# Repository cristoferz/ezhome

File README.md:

# ezHome Project 

This is the home for the ezHome team's development.

### Project status

For now, the project is on the beginning so there's not much to talk about.
We are developing the basis for customization capabilitys, communication standarts and somethings like that. 

More details can be founded on Issues.

## See also ##
[Project Pieces](PROJECT_PIECES.md)

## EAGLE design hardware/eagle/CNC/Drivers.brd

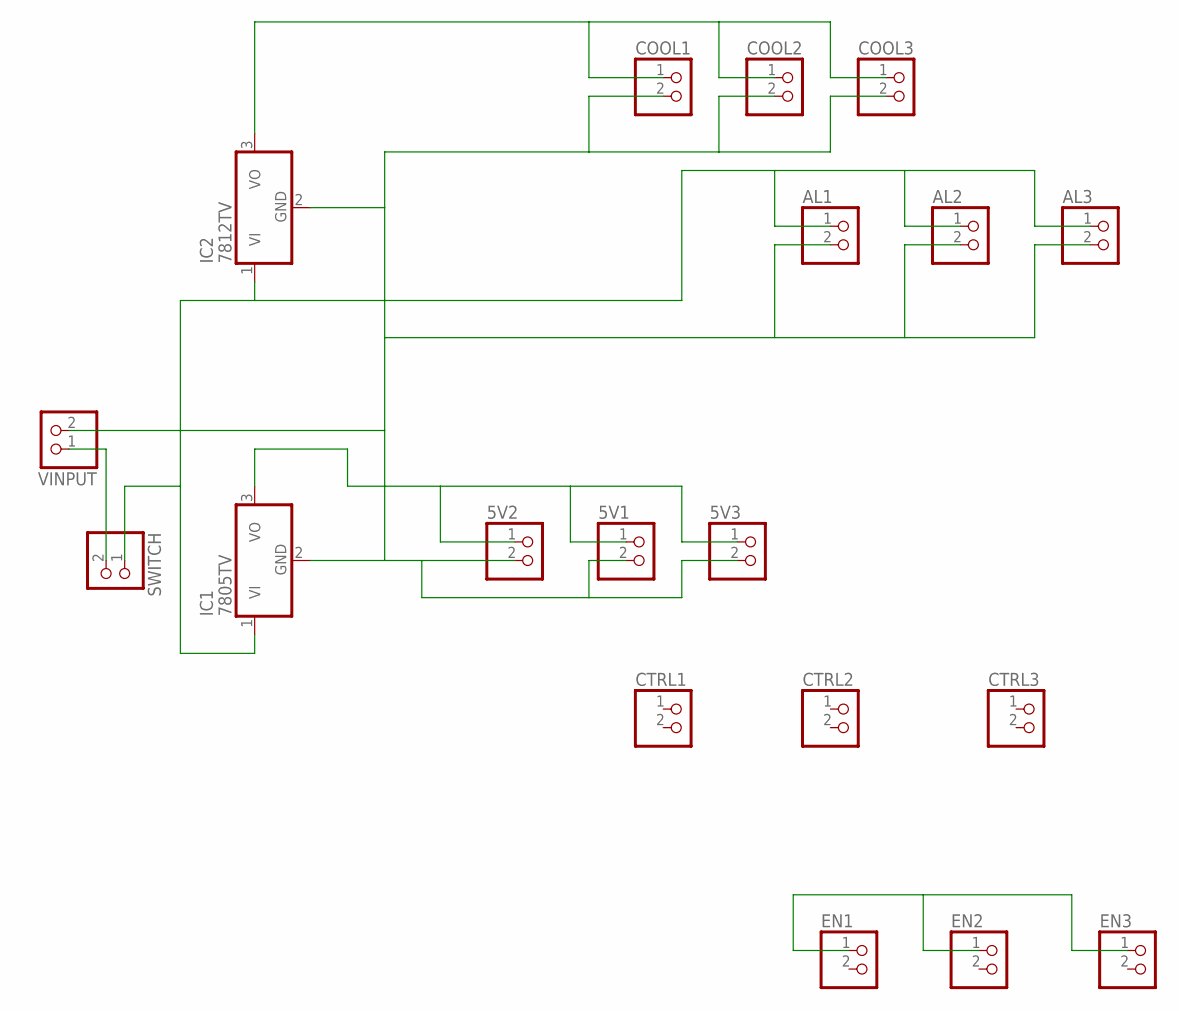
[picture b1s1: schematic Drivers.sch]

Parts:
5V1, 5V2, 5V3: PINHD-1X2; 1X02
AL1, AL2, AL3: PINHD-1X2; 1X02
COOL1, COOL2, COOL3: PINHD-1X2; 1X02
CTRL1, CTRL2, CTRL3: PINHD-1X2; 1X02
EN1, EN2, EN3: PINHD-1X2; 1X02
IC1: 7805TV; TO220V
IC2: 7812TV; TO220V
SWITCH: PINHD-1X2; 1X02
VINPUT: PINHD-1X2; 1X02

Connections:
unnamed: 5V1.2, 5V2.2, 5V3.2, AL1.2, AL2.2, AL3.2, COOL1.2, COOL2.2, COOL3.2, IC1.2 (GND), IC2.2 (GND), VINPUT.2
unnamed: 5V1.1, 5V2.1, 5V3.1, IC1.3 (VO)
unnamed: EN1.1, EN2.1, EN3.1
unnamed: AL1.1, AL2.1, AL3.1, IC1.1 (VI), IC2.1 (VI), SWITCH.1
unnamed: SWITCH.2, VINPUT.1
unnamed: COOL1.1, COOL2.1, COOL3.1, IC2.3 (VO)

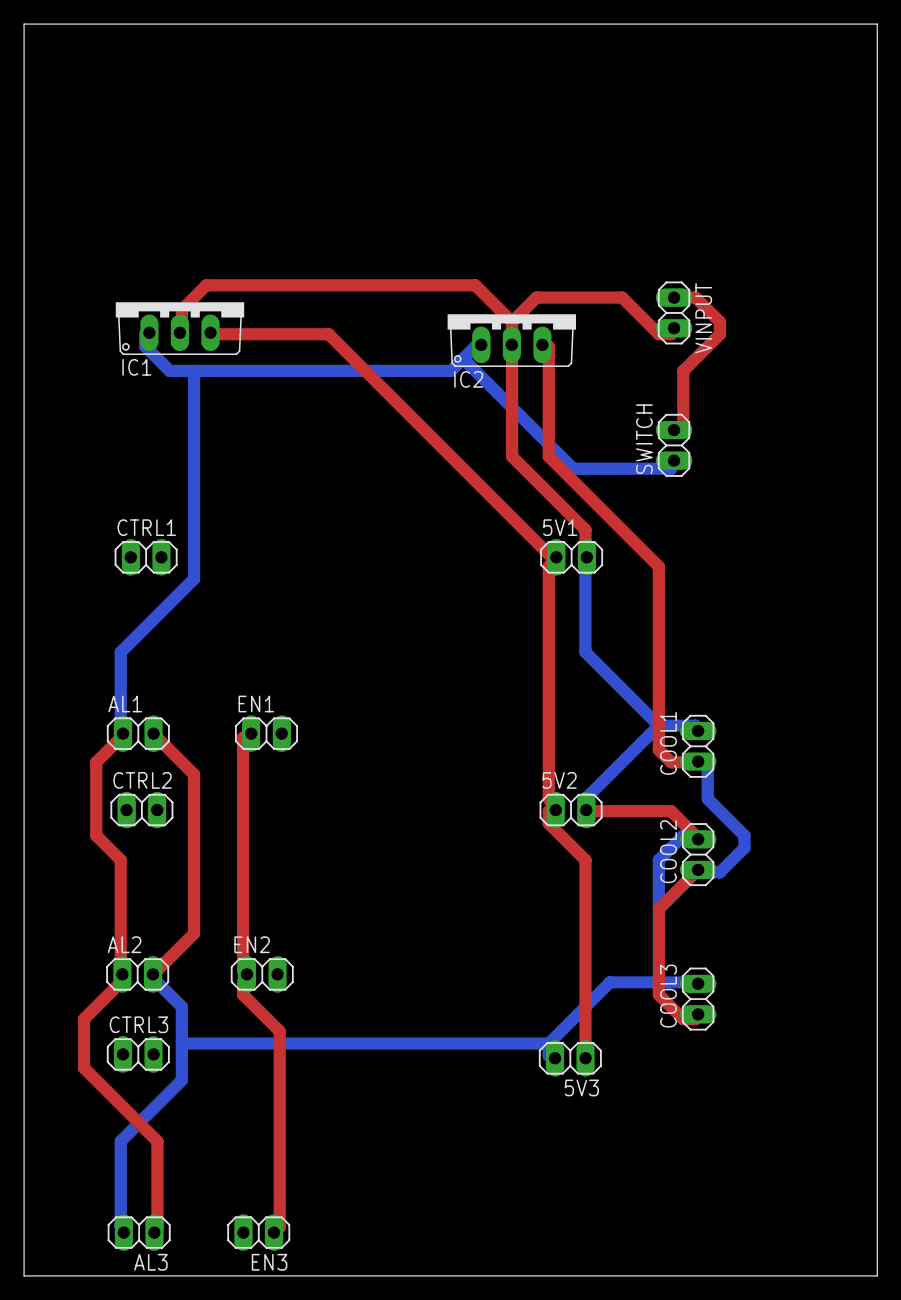
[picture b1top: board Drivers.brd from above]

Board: 2 copper layers, 70.9 x 104.0 mm, 19 parts (0 on the bottom side), 6 nets.

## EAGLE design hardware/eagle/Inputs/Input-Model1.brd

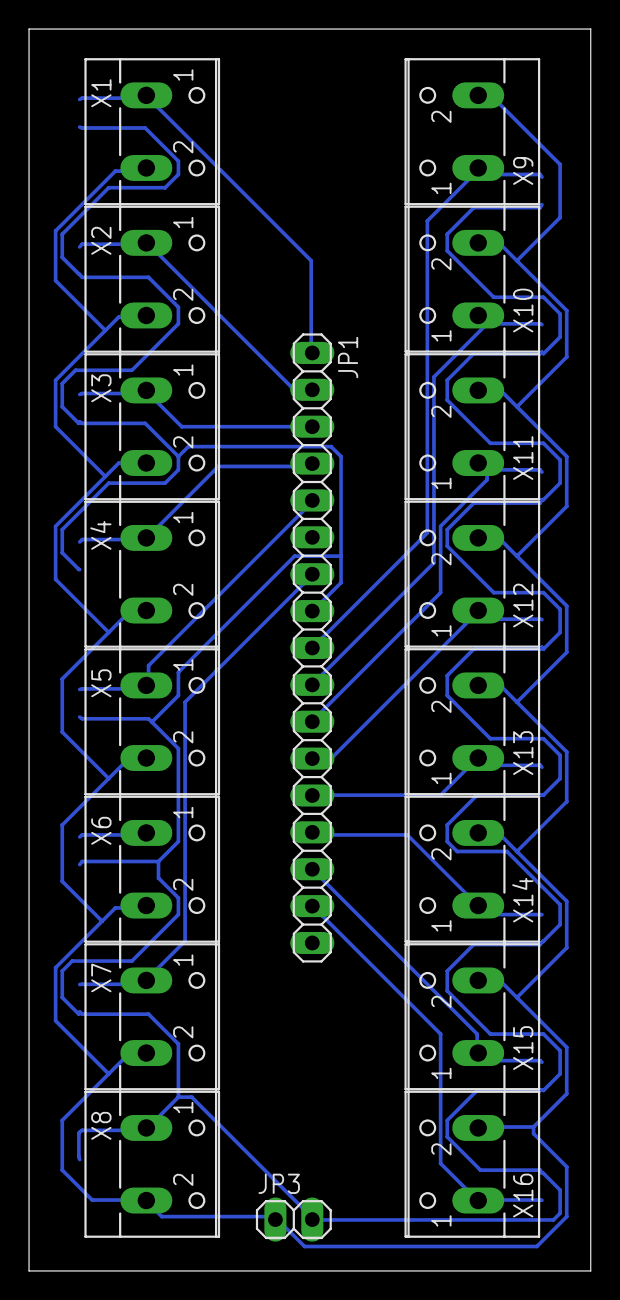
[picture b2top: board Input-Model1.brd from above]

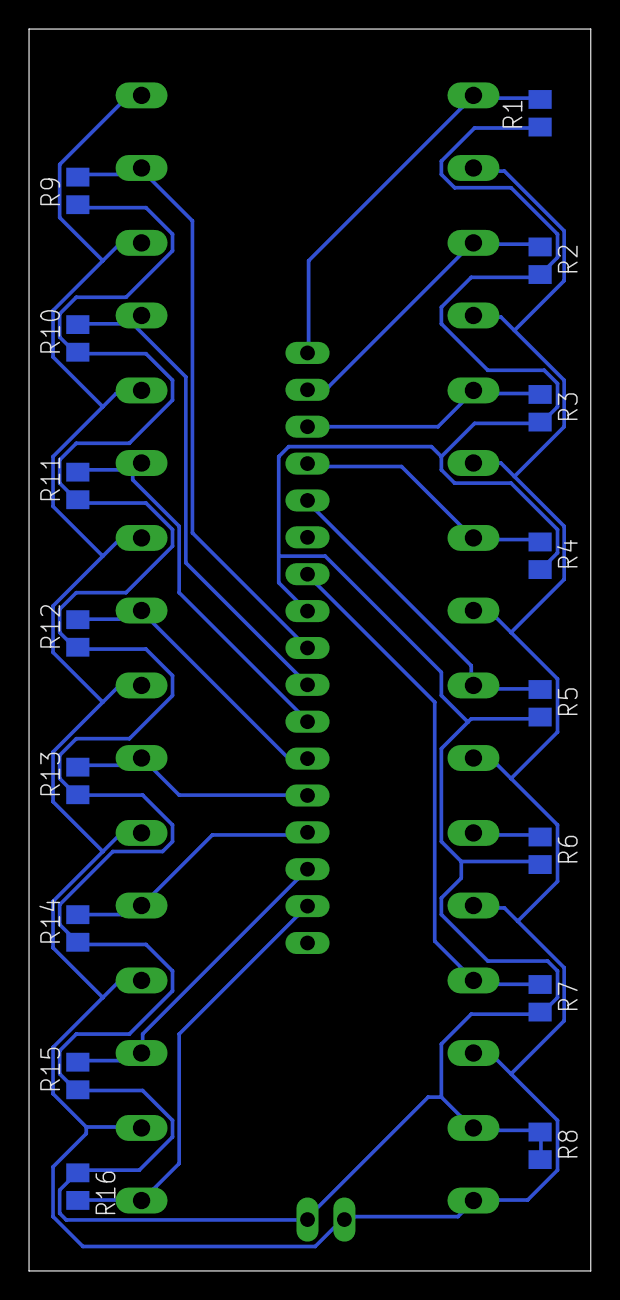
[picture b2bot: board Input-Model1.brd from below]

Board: 2 copper layers, 38.7 x 85.5 mm, 34 parts (16 on the bottom side), 17 nets.

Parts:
JP1: 1X17
JP3: 1X02
R1, R2, R3, R4, R5, R6, R7, R8, R9, R10, R11, R12, R13, R14, R15, R16: M0805
X1, X2, X3, X4, X5, X6, X7, X8, X9, X10, X11, X12, X13, X14, X15, X16: W237-102

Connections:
unnamed: JP1.1, R1.2, X1.1
unnamed: JP1.8, JP3.2, R1.1, R2.2, R3.2, R4.2, R5.2, R6.2, R7.2, R8.1, R8.2, R9.1, R10.1, R11.1, R12.1, R13.1, R14.1, R15.1, R16.1, X8.1
unnamed: JP3.1, X1.2, X2.2, X3.2, X4.2, X5.2, X6.2, X7.2, X8.2, X9.2, X10.2, X11.2, X12.2, X13.2, X14.2, X15.2, X16.2
unnamed: JP1.2, R2.1, X2.1
unnamed: JP1.3, R3.1, X3.1
unnamed: JP1.4, R4.1, X4.1
unnamed: JP1.5, R5.1, X5.1
unnamed: JP1.7, R7.1, X7.1
unnamed: JP1.6, R6.1, X6.1
unnamed: JP1.16, R16.2, X16.1
unnamed: JP1.9, R9.2, X9.1
unnamed: JP1.10, R10.2, X10.1
unnamed: JP1.11, R11.2, X11.1
unnamed: JP1.12, R12.2, X12.1
unnamed: JP1.13, R13.2, X13.1
unnamed: JP1.14, R14.2, X14.1
unnamed: JP1.15, R15.2, X15.1

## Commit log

2016-02-18 Initial commit with contributors
2016-02-18 Estrutura de base do controlador
2016-02-18 Testes de comunicação com a porta serial
2016-02-19 Testes de leitura do RXTX
2016-02-20 Adicionados os fontes originais para o arduino
2016-02-20 Levantamentos e regras analisadas acerca dos componentes, controladores e nomenclaturas do projeto
2016-02-22 Alterações para a leitura da porta Serial
2016-02-26 Restaurando a versão original do arduino
2016-02-29 Implementados os comandos de comunicação com o Arduino
2016-03-14 v1 da programação do Controlador Master
2016-03-29 Boxes para alocação do raspberry e arduinos
2016-04-04 Adicionadas as funcionalidades: - Parallel Series - Interpretação do JSON para programação
2016-04-04 Adicionada a programação de valores numericos (a concluir)
2016-04-04 Adicionado o .gitignore
2016-04-13 Caixas
2016-04-13 Adicionadas as paredes para o suporte
2016-04-21 Alteraçoes da caixa
2016-04-28 Adicionada a função de programação remota
2016-05-01 Adicionadas as funcionalidades de FallingEdge e RisingEdge ao interpretador de JSON Ladder
2016-05-03 Adicionada a Caixa V3
2016-05-07 Removida a mensagem invalida
2016-05-08 Adicionado o encaixe de parafuso para fixação
2016-05-12 Adicionado o projeto de inputs
2016-05-19 Module configuration
2016-06-01 Melhorias nos processos de comunicação com o Arduino
2016-06-01 Added ionic new project
2016-06-02 Test-site created for testing with angular2
2016-06-11 Multiplas alterações
2016-06-11 Added README file
2016-06-11 Project pieces definition
2016-06-11 README.md edited online with Bitbucket
2016-06-11 Project pieces reorganizations
2016-06-11 Added initial documentations for project
2016-06-11 Reviewing arduino communication protocols
2016-06-11 Major fixes and refactoring of device operations
2016-06-11 First version of CONTRIBUTING.md. Needs revision
2016-06-12 Initial tests
2016-06-12 Added Access-Control-Allow-Origin=* to allow remote access to controller Webservice
2016-06-12 Basic development of local configuration site
2016-06-17 Adjustments
2016-06-17 Added the device communication protocol documentation.
2016-06-17 Added README and initial version of JSON_LADDER protocol description
2016-06-18 Testing table of contents
2016-06-18 Added full table of contents for PROTOCOL and minor formation fixes to documentation.
2016-06-25 Removed the mock-devices
2016-06-28 Adjusted gitignore
2016-06-29 Reorganized functions for controller
2016-06-29 Update library references to relative paths and correcting source code error.
2016-06-29 Creating base structure for build .deb package for ezHomeController
2016-06-30 Adjusting release structures and added ezHome daemon
2016-07-01 Adjusted Makefile for generating services and startup configs
2016-07-01 Final adjustments
2016-07-01 Sintax adjustments
2016-07-02 Improvements on service initialization
2016-07-02 Created default http handler for local config site
2016-07-04 Created classes fr JWT authentication
2016-07-04 Minor adjustments
2016-07-04 Backend adjustments
2016-08-31 Commit restoration
2016-08-31 - Commit restoration
2016-09-02 Added Counter class
2016-09-09 devices: Add counter implementation
2016-09-13 Added comparator to devices Changed NC and NO interpreters to their own classes
2016-09-13 Added math operations according to issue 15
2016-09-15 Improved documentation for JSON Ladder protocol
2016-09-18 Restructuring JSON Ladder manual and adding SetReset instruction
2016-09-18 Added Timers and Counters
2016-09-19 Added MathOperation and Comparators
2016-10-17 Added Bouncy Castle library for certificate generation
2016-10-18 Divided libraries from controller to allow creation of custom libraries by users
2016-11-05 Added holes on relay box
2016-11-14 issue13: implementation of ezHomeCompiler.
2016-11-14 ignore adjustments
2016-11-15 controller: adjusted .deb installer for full instalation on raspberry pi
2016-11-15 controller: adjustments for ezhome installer
2016-11-15 Adjusting logs
2016-11-15 Added example local-site with angular-cli
2016-12-07 Added support for Angular 2 with routing
2017-03-08 added capability for reading DS18B20 sensors
2017-03-08 Added DS18B20 sensors
2017-04-10 Pending changes
